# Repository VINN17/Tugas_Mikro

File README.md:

# 🚧 Building Automation System (BAS) untuk Pompa Air Jalan Tol
### Solusi Banjir dan Kemacetan saat Hujan Berkepanjangan

<div align="center">
  
</div>

                                                    https://github.com/user-attachments/assets/4135e06a-734f-496c-8481-714472587500

## 📚 Daftar Isi

1. [📌 Deskripsi Proyek](#-deskripsi-proyek)
2. [🎯 Tujuan Proyek](#-tujuan-proyek)
3. [🛠️ Teknologi dan Komponen](#️-teknologi-dan-komponen)
4. [⚙️ Cara Kerja Sistem](#️-cara-kerja-sistem)
5. [🧩 Diagram Alur Sistem](#-diagram-alur-sistem)
6. [🌟 Keunggulan Proyek](#-keunggulan-proyek)
7. [📈 Potensi Pengembangan](#-potensi-pengembangan)
8. [🤝 Kolaborasi & Dukungan](#-kolaborasi--dukungan)
9. [👥 Struktur Tim](#-struktur-tim)
10. [📩 Hubungi Kami](#-hubungi-kami)

---

## 📌 Deskripsi Proyek

**Building Automation Systems** ini dirancang untuk mengotomatisasi pengoperasian **pompa air pada jalan tol** guna mengatasi genangan atau banjir secara cepat dan efisien.

Dengan memanfaatkan sensor debit dan volume air, sistem ini mampu menghidupkan atau mematikan pompa secara otomatis berdasarkan data real-time, sehingga meningkatkan **keamanan** dan **kenyamanan** pengguna jalan.

> Dikembangkan berbasis **Arduino Uno** dan sistem monitoring berbasis GUI, proyek ini menawarkan solusi otomasi yang **andal**, **efisien**, dan **mudah diimplementasikan**.

---

## 🎯 Tujuan Proyek

* **Efisiensi Operasional Maksimal**
  Sistem mengeliminasi keterlambatan manual dan mengoptimalkan respons terhadap kondisi air.

* **Minimalkan Risiko Human Error**
  Pengambilan keputusan berbasis data sensor menghindari kesalahan dalam penanganan banjir.

* **Solusi Otomasi Biaya Terjangkau**
  Menggunakan komponen yang tersedia di pasaran dengan biaya rendah, ideal untuk skalabilitas.

---

## 🛠️ Teknologi dan Komponen

| Komponen           | Spesifikasi                                  |
| ------------------ | -------------------------------------------- |
| Mikrokontroler     | Arduino Uno                                  |
| Sensor Debit Air   | Pressure Sensor                              |
| Sensor Volume Air  | Ultrasonic / Water Level Sensor              |
| Aktuator           | Pompa Air + Relay Module                     |
| Antarmuka Pengguna | GUI berbasis Figma (Start/Stop, Monitoring)  |
| Komunikasi Data    | Serial / Wireless (pengembangan selanjutnya) |

---

## ⚙️ Cara Kerja Sistem

1. Sensor membaca **debit** dan **volume air** secara berkala.
2. Data dikirim ke mikrokontroler dan dibandingkan dengan nilai **set point**.
3. **Logika Kendali Otomatis**:

   * Jika data melebihi ambang → **Pompa ON**
   * Jika data aman → **Pompa OFF**
4. Status sistem ditampilkan pada GUI untuk **monitoring real-time**.
5. Operator dapat melakukan **manual override** dari GUI bila dibutuhkan.

---

## 🧩 Diagram Alur Sistem

**Penjelasan Alur:**

* Sistem dimulai melalui tampilan GUI.

* Pengguna memilih mode: **Auto** atau **Manual**.

  * **Auto**: sensor membaca data → kirim ke GUI → kontrol pompa otomatis.
  * **Manual**: pengguna dapat menyalakan/mematikan pompa secara langsung.

* Sistem akan terus berjalan sampai dihentikan manual oleh operator.

---

## 💻 PCB

Diatas  merupakan desain PCB jadi 

---

## 🌟 Keunggulan Proyek

* ✅ **Respon Real-Time** terhadap potensi banjir.
* ✅ **Kontrol Terpusat & Mudah** dari satu GUI.
* ✅ **Terintegrasi dengan IoT/SCADA** untuk masa depan.
* ✅ **Desain Scalable** & mudah diadaptasi ke area baru.
* ✅ **Ramah Anggaran** untuk implementasi massal.

---

## 📈 Potensi Pengembangan

* 🌐 **Integrasi ke IoT Cloud**: akses global & notifikasi otomatis.
* 🔔 **Peringatan SMS/WhatsApp** saat kondisi kritis.
* 🧠 **Prediksi Banjir Berbasis AI**: analisis historis dengan Machine Learning.
* 🏙️ **Kompatibel dengan Smart City Infrastructure**.

---

## 🤝 Kolaborasi & Dukungan

Kami membuka peluang kerja sama dengan:

* 🔧 **Investor teknologi** yang tertarik pada otomasi infrastruktur.
* 🛣️ **Pemerintah / Operator Jalan Tol** untuk penerapan langsung.
* 🧪 **Startup atau perusahaan R\&D** yang ingin mengembangkan solusi pintar dan berdampak.

> 🎯 Kami siap melakukan presentasi, demo proyek, dan diskusi lanjutan bersama mitra strategis.

---

## 👥 Struktur Tim

| NRP        | Nama    | Peran Utama              |
| ---------- | ------- | ------------------------ |
| 2123600010 | Imam    | Project Manager          |
| 2123600014 | Ferri   | Desain PCB               |
| 2123600004 | Robith  | Spesialis Hardware       |
| 2123600030 | Zach    | Pengembang Software      |
| 2123600023 | Choirul | Desainer 3D              |
| 2123600019 | Andira  | Non-Teknis & Dokumentasi |

---

## 📩 Hubungi Kami

📧 Untuk kerja sama, pertanyaan, atau demo proyek:

**Email Project Manager**: [immarfn17@gmail.com](mailto:immarfn17@gmail.com)

https://github.com/user-attachments/assets/88c9bd39-f75d-4216-a4de-ee6d6c01959d
> 🚀 Mari bersama kita ciptakan masa depan infrastruktur jalan tol yang lebih **cerdas**, **aman**, dan **berkelanjutan**.

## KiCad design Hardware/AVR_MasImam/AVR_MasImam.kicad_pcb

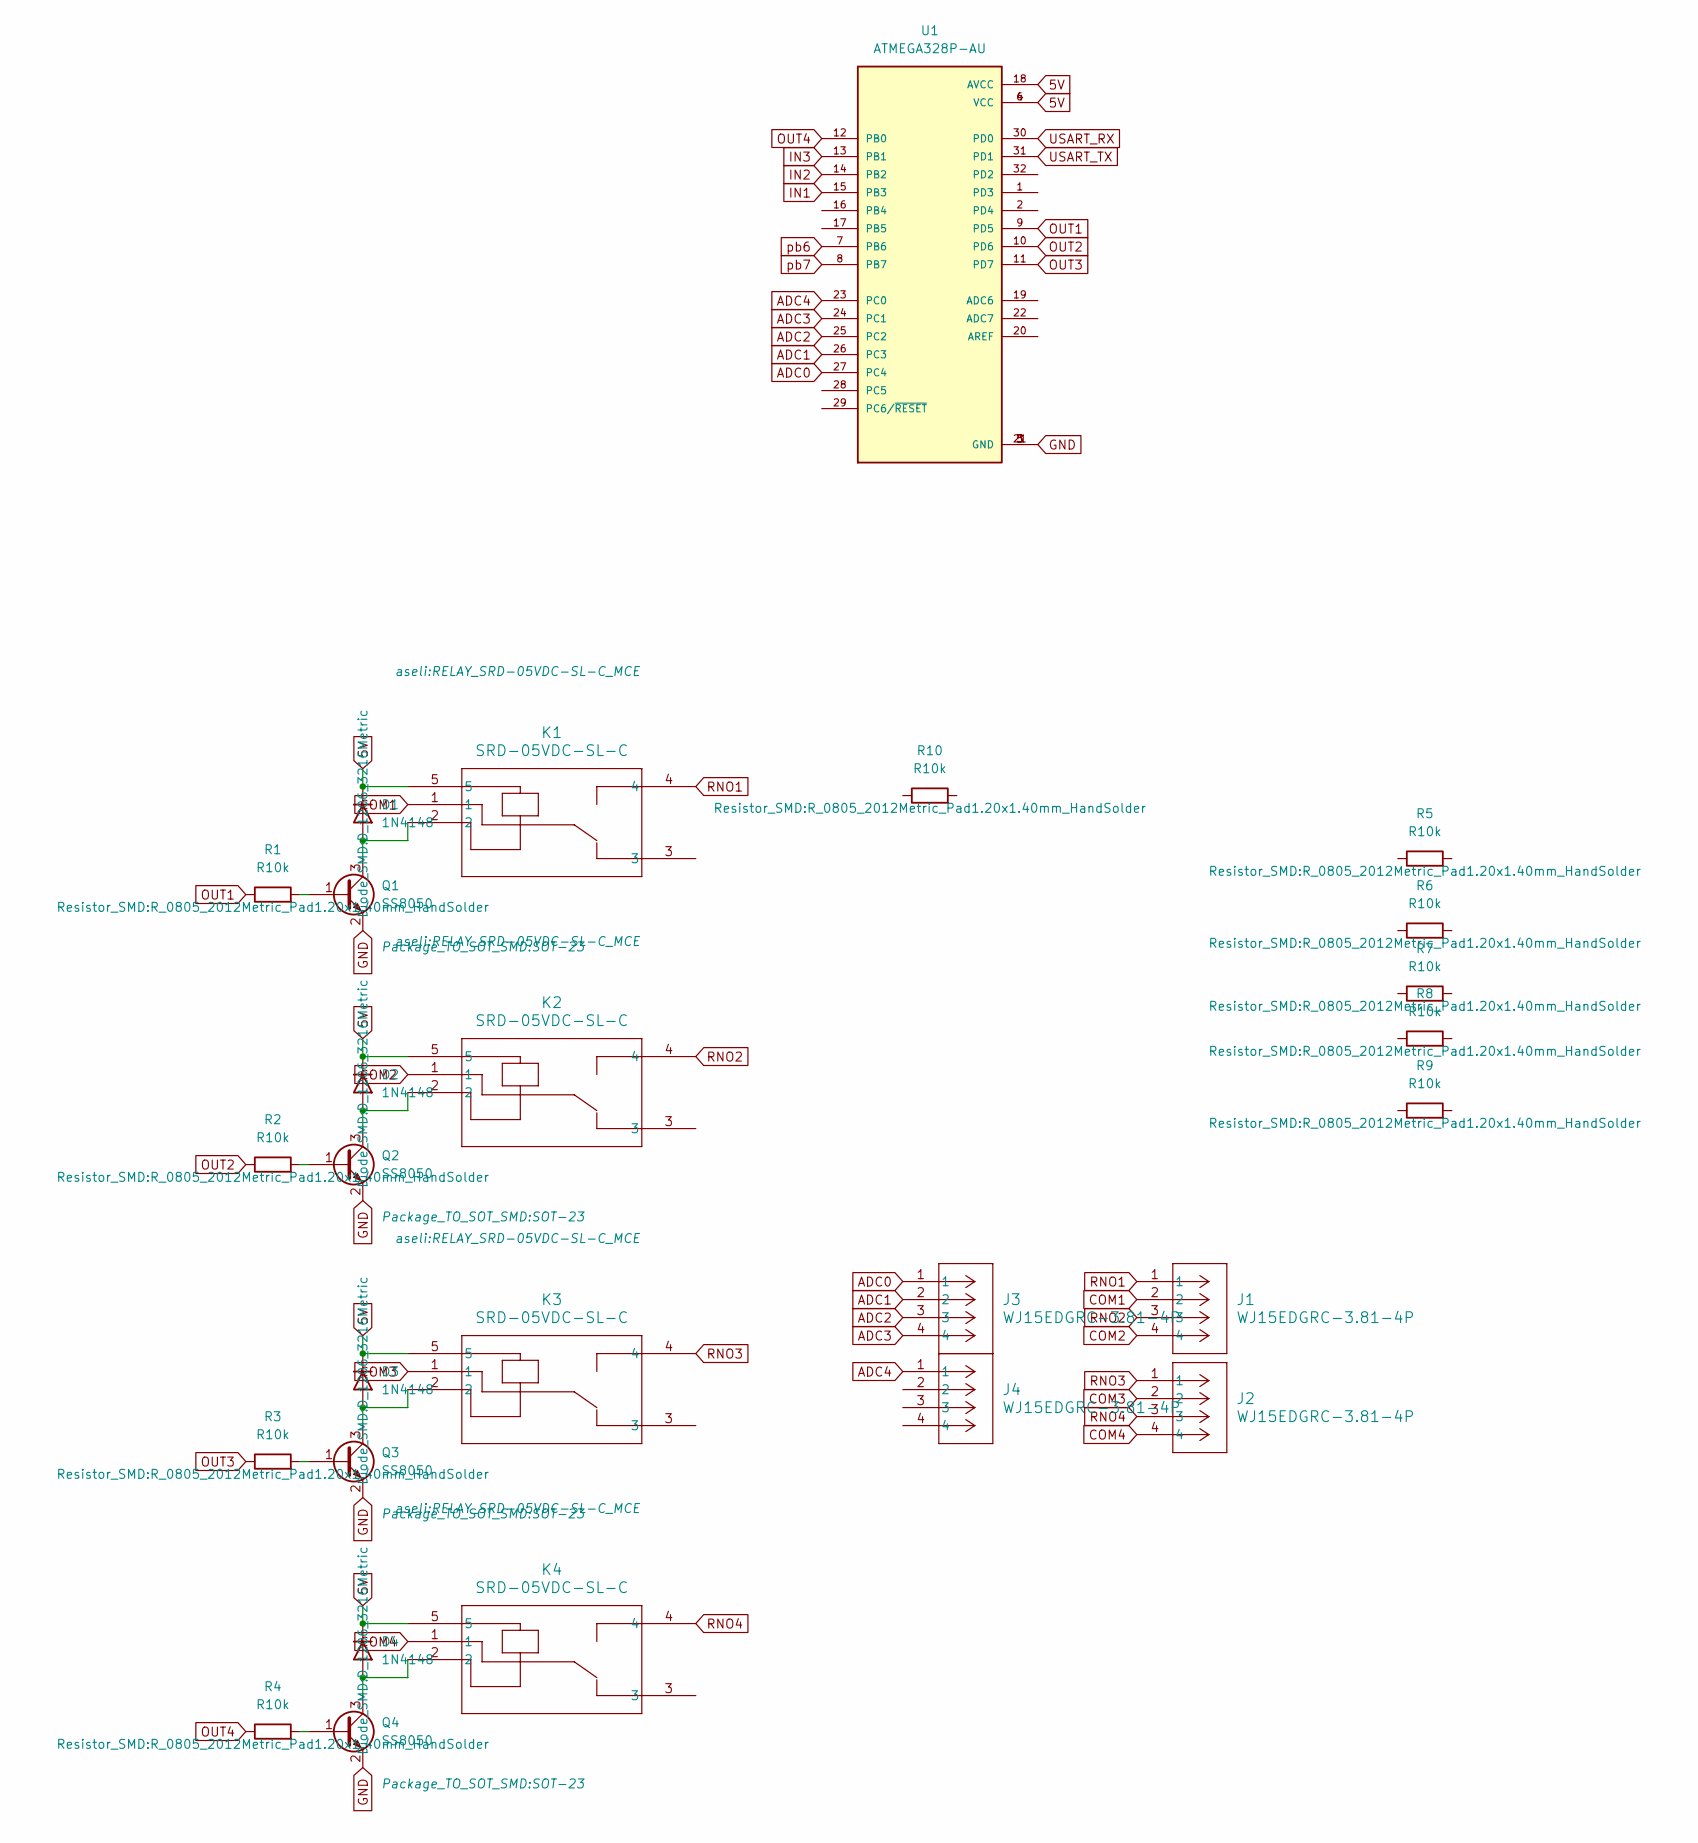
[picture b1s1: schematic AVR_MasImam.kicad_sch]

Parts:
D1, D2, D3, D4: 1N4148; D_1206_3216Metric
J1, J2, J3, J4: WJ15EDGRC-3.81-4P; CONN_WJ15EDGRC-3.81-4P_KAN
K1, K2, K3, K4: SRD-05VDC-SL-C; RELAY_SRD-05VDC-SL-C_MCE
Q1, Q2, Q3, Q4: SS8050; SOT-23
R1, R2, R3, R4, R5, R6, R7, R8, R9, R10: R10k; R_0805_2012Metric_Pad1.20x1.40mm_HandSolder
U1: ATMEGA328P-AU; QFP80P900X900X120-32N; PARTREV 8271A

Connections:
5V: D1.1 (K), D2.1 (K), D3.1 (K), D4.1 (K), K1.5, K2.5, K3.5, K4.5, U1.4 (VCC), U1.6 (VCC), U1.18 (AVCC); also elsewhere on the board
ADC0: J3.1, R5.2, U1.27 (PC4); also elsewhere on the board
ADC1: J3.2, R6.2, U1.26 (PC3); also elsewhere on the board
ADC2: J3.3, R7.2, U1.25 (PC2); also elsewhere on the board
ADC3: J3.4, R8.2, U1.24 (PC1); also elsewhere on the board
ADC4: J4.1, R9.2, U1.23 (PC0); also elsewhere on the board
COM1: J1.2, K1.1
COM2: J1.4, K2.1
COM3: J2.2, K3.1
COM4: J2.4, K4.1
GND: Q1.2 (E), Q2.2 (E), Q3.2 (E), Q4.2 (E), R5.1, R6.1, R7.1, R8.1, R9.1, U1.3 (GND), U1.5 (GND), U1.21 (GND); also elsewhere on the board
unnamed: D1.2 (A), K1.2, Q1.3 (C)
unnamed: D2.2 (A), K2.2, Q2.3 (C)
unnamed: D3.2 (A), K3.2, Q3.3 (C)
unnamed: D4.2 (A), K4.2, Q4.3 (C)
unnamed: Q1.1 (B), R1.2
unnamed: Q2.1 (B), R2.2
unnamed: Q3.1 (B), R3.2
unnamed: Q4.1 (B), R4.2
OUT1: R1.1, U1.9 (PD5); also elsewhere on the board
OUT2: R2.1, U1.10 (PD6); also elsewhere on the board
OUT3: R3.1, U1.11 (PD7); also elsewhere on the board
OUT4: R4.1, U1.12 (PB0); also elsewhere on the board
RNO1: J1.1, K1.4
RNO2: J1.3, K2.4
RNO3: J2.1, K3.4
RNO4: J2.3, K4.4

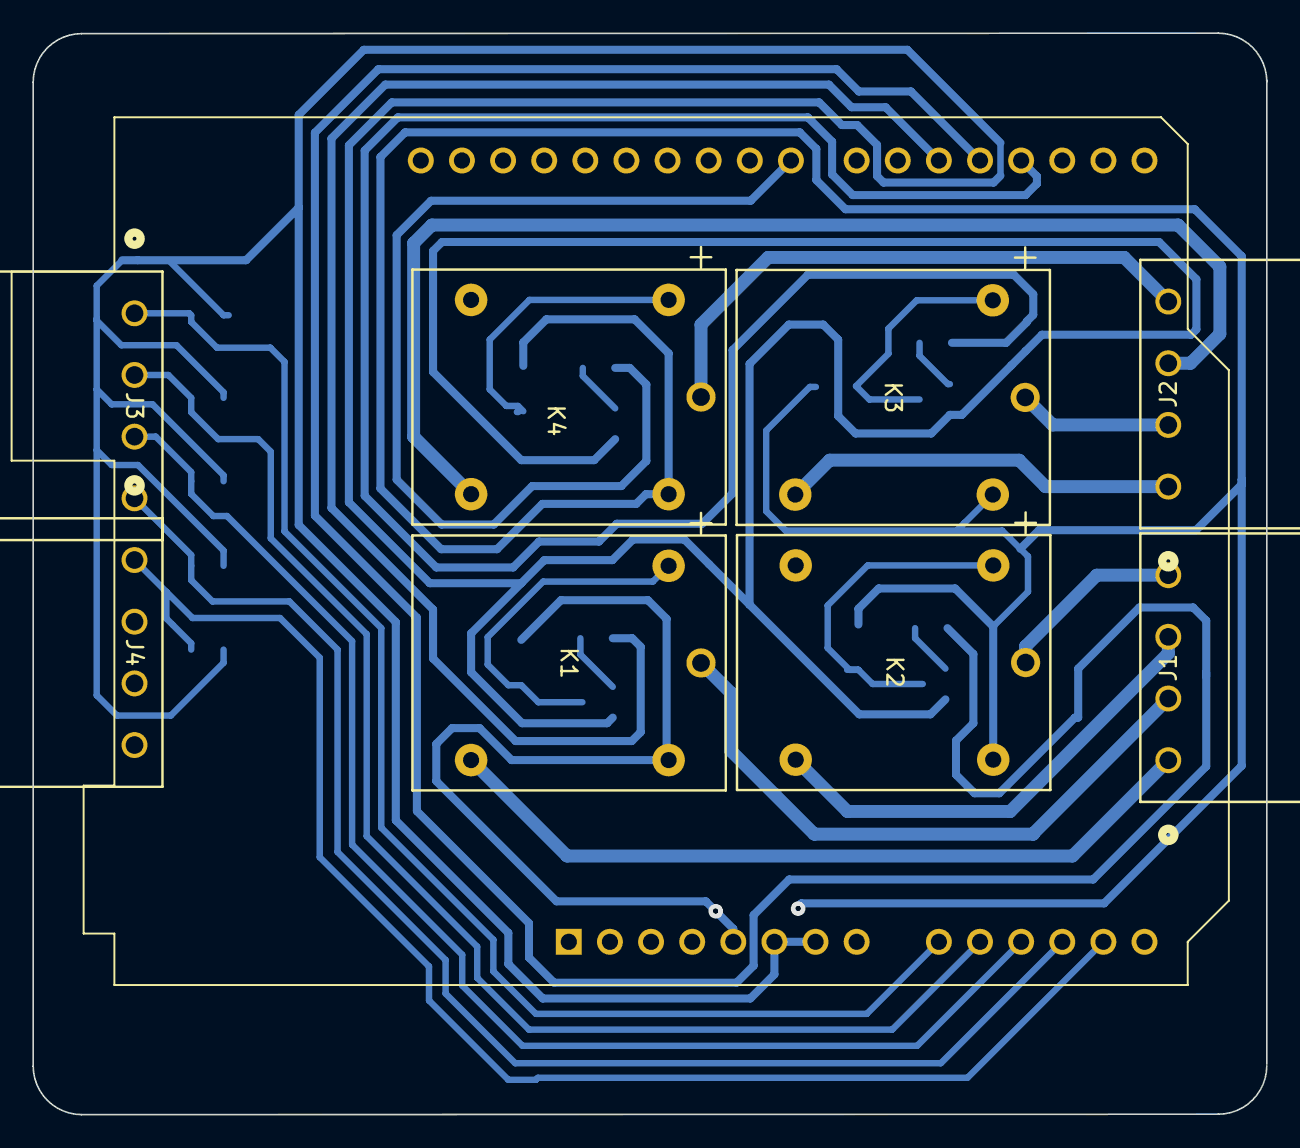
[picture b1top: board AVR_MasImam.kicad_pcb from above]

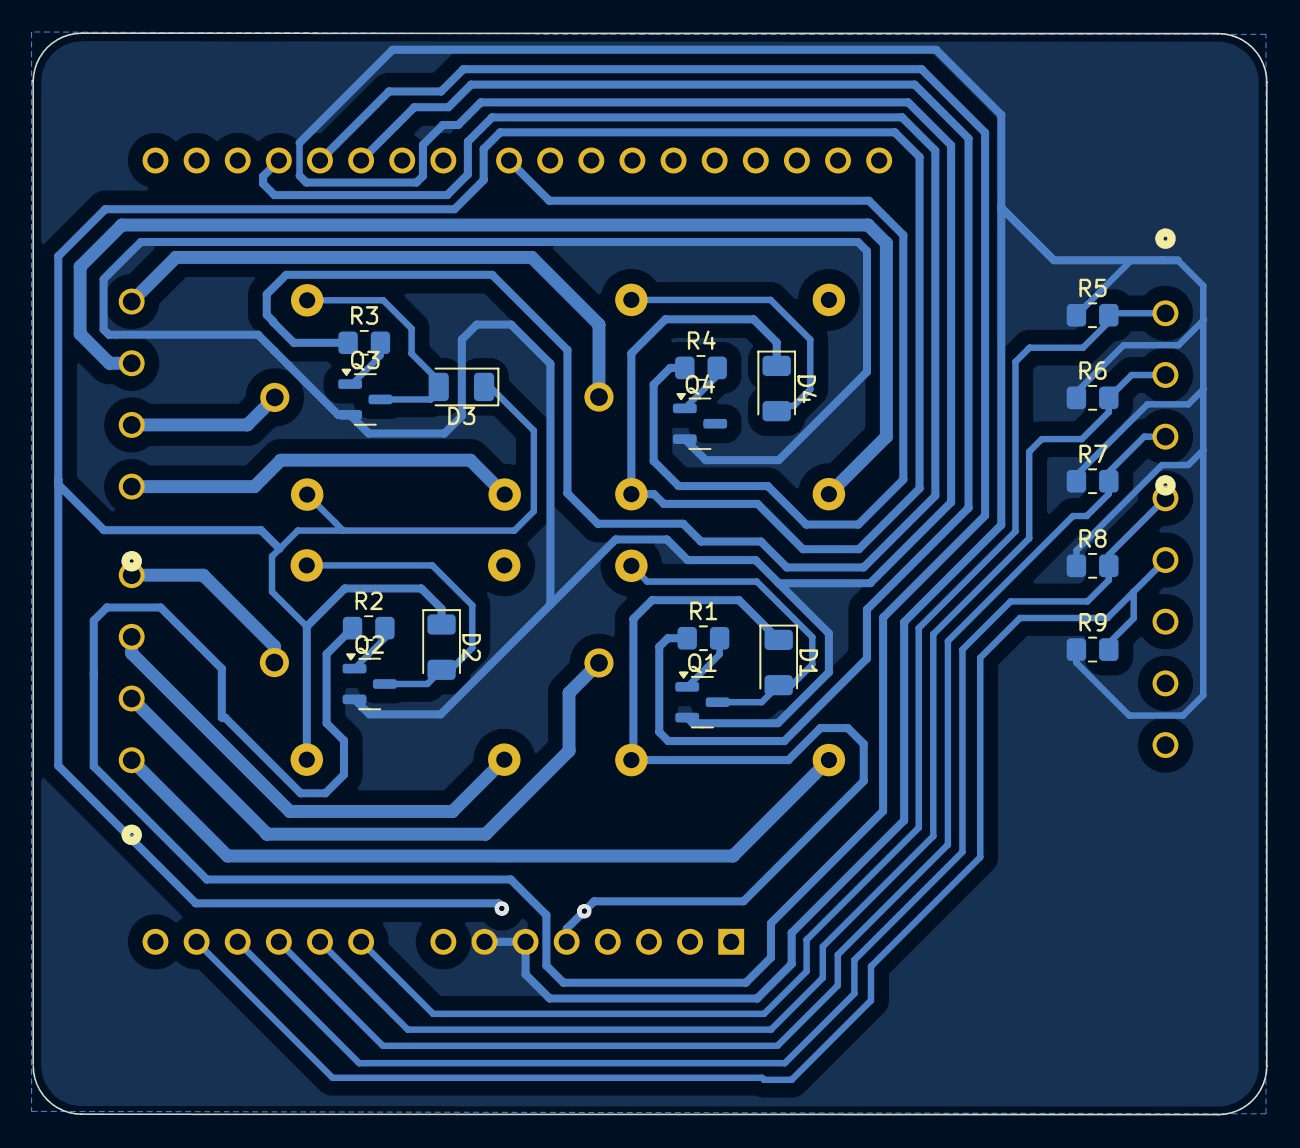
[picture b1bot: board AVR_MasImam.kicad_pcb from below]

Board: 2 copper layers, 76.2 x 66.8 mm, 26 parts (17 on the bottom side), 27 nets.

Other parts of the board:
A1: Arduino_UNO_R3

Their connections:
5V: A1.5 (+5V); also elsewhere on the board
ADC0: A1.9 (A0); also elsewhere on the board
ADC1: A1.10 (A1); also elsewhere on the board
ADC2: A1.11 (A2); also elsewhere on the board
ADC3: A1.12 (A3); also elsewhere on the board
ADC4: A1.13 (SDA/A4); also elsewhere on the board
GND: A1.6 (GND), A1.7 (GND); also elsewhere on the board
OUT1: A1.20 (D5); also elsewhere on the board
OUT2: A1.19 (D4); also elsewhere on the board
OUT3: A1.18 (D3); also elsewhere on the board
OUT4: A1.23 (D8); also elsewhere on the board

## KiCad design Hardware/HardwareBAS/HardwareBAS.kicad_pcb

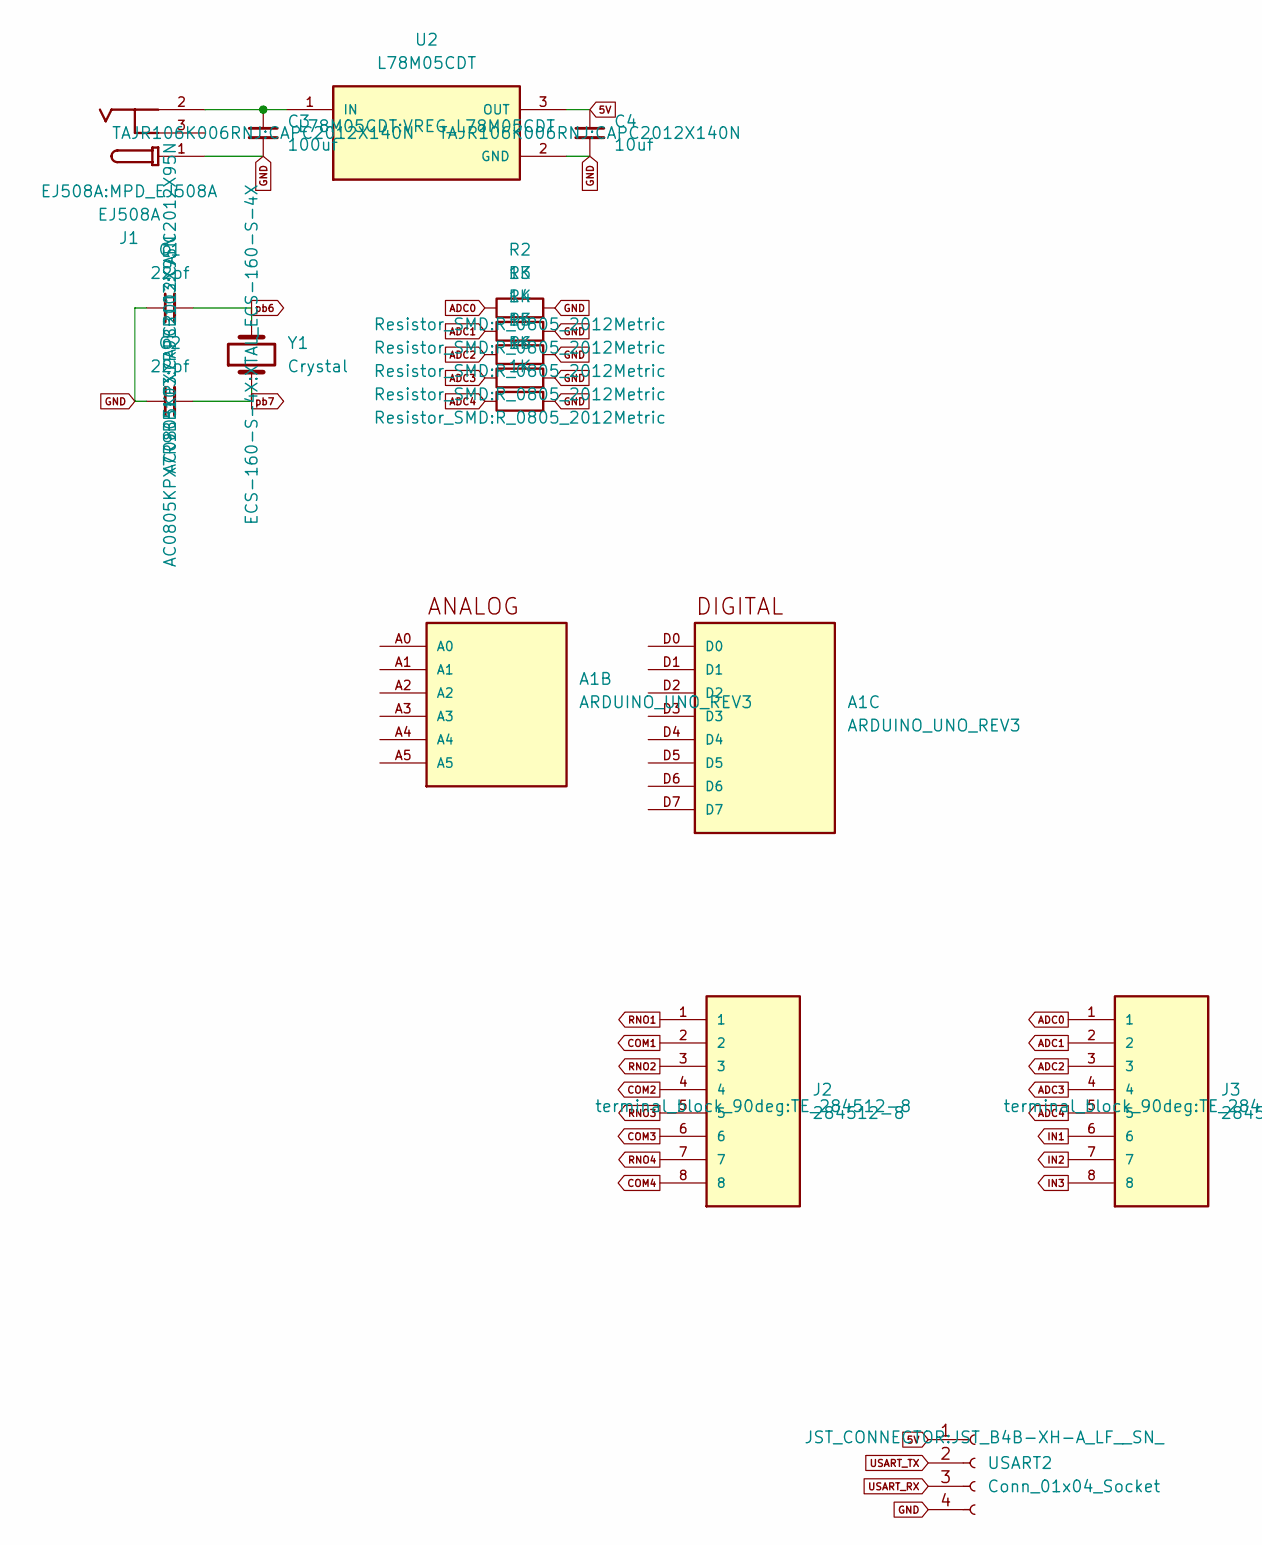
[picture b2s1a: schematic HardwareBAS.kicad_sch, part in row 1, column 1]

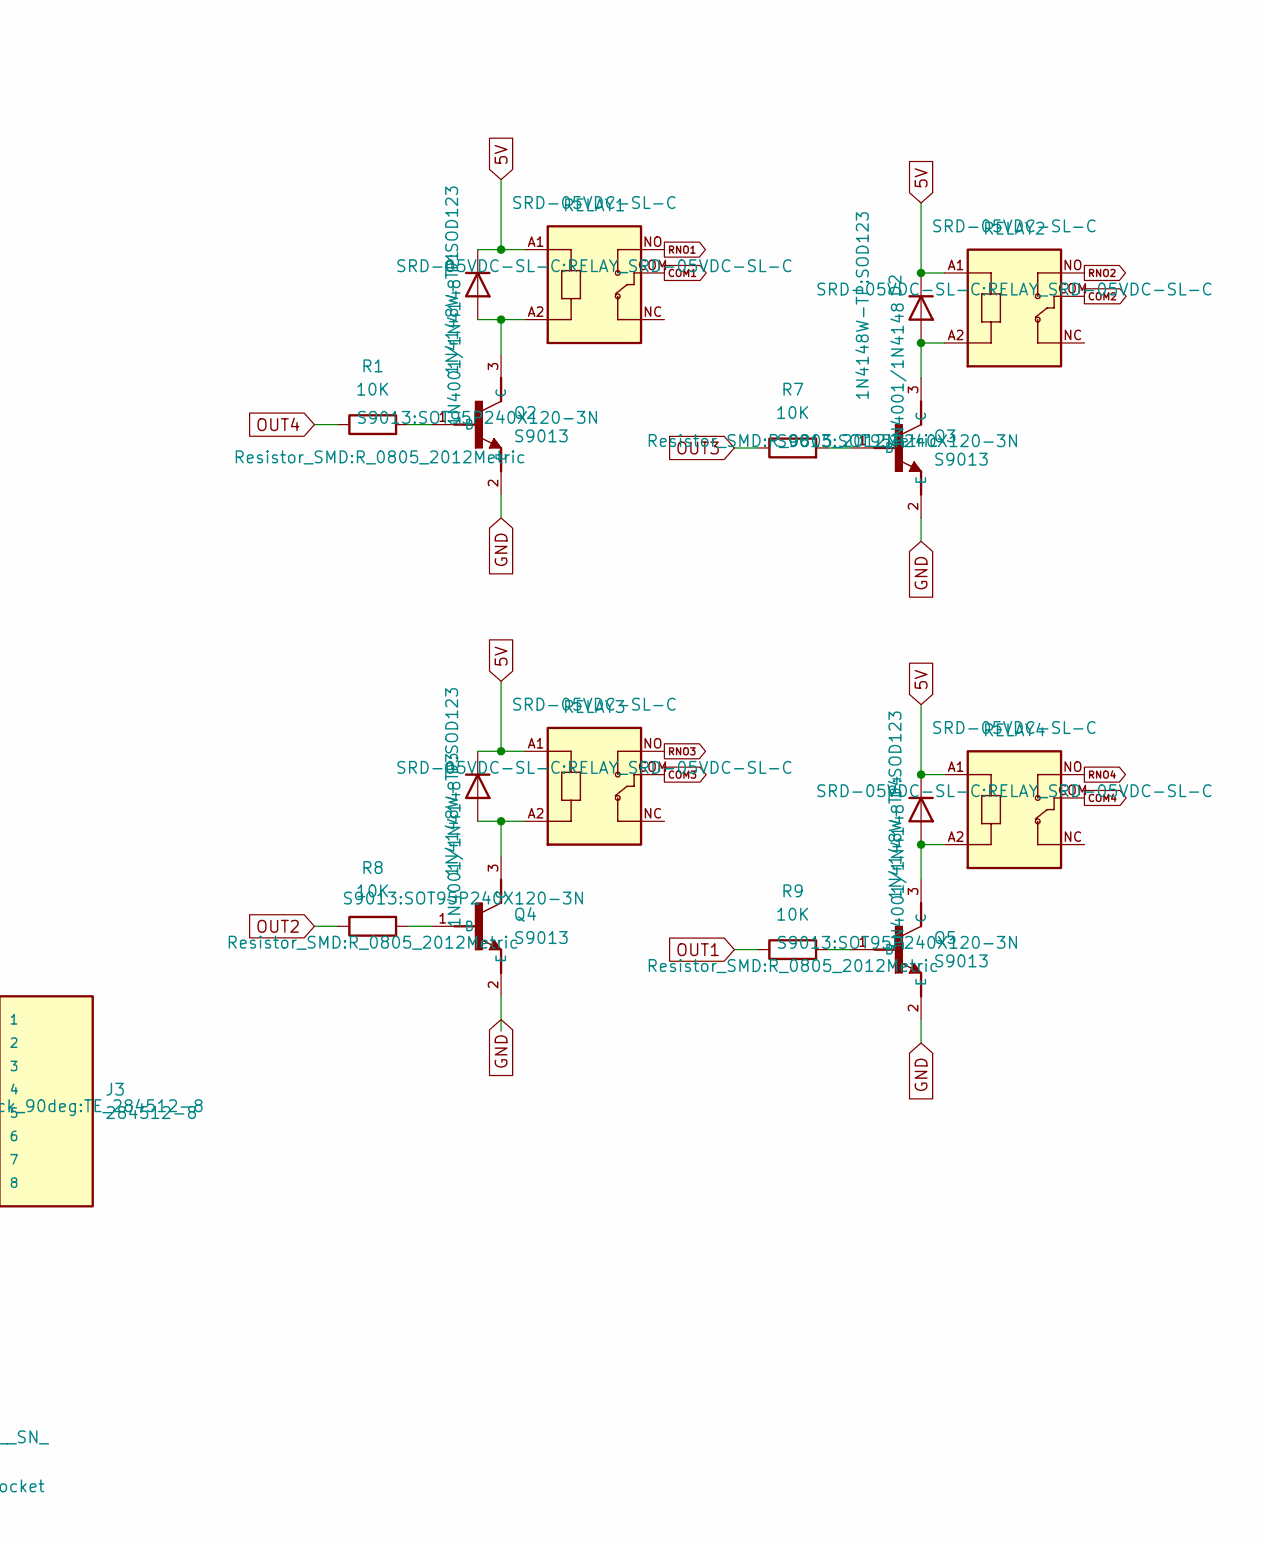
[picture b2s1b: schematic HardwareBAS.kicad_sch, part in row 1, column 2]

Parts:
A1: ARDUINO_UNO_REV3; ARDUINO_ARDUINO_UNO_REV3; PARTREV N/A
C1, C2: 22pf; CAPC2012X95N
C3: 100uf; CAPC2012X140N
C4: 10uf; CAPC2012X140N
D1, D2, D3, D4: 1N4001/1N4148; SOD123
J1: EJ508A; MPD_EJ508A; PARTREV J
J2, J3: 284512-8; TE_284512-8; PARTREV R
Q2, Q3, Q4, Q5: S9013; SOT95P240X120-3N
R1, R7, R8, R9: 10K; R_0805_2012Metric
R2, R3, R4, R5, R6: 1K; R_0805_2012Metric
RELAY1, RELAY2, RELAY3, RELAY4: SRD-05VDC-SL-C; RELAY_SRD-05VDC-SL-C
U2: L78M05CDT; VREG_L78M05CDT; PARTREV 24
USART2: Conn_01x04_Socket; JST_B4B-XH-A_LF__SN_
Y1: Crystal; XTAL_ECS-160-S-4X

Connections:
5V: C4.1, D1.1 (K), D2.1 (K), D3.1 (K), D4.1 (K), RELAY1.A1, RELAY2.A1, RELAY3.A1, RELAY4.A1, U2.3 (OUT), USART2.1
ADC0: J3.1, R2.1
ADC1: J3.2, R3.1
ADC2: J3.3, R4.1
ADC3: J3.4, R5.1
ADC4: J3.5, R6.1
COM1: J2.2, RELAY1.COM
COM2: J2.4, RELAY2.COM
COM3: J2.6, RELAY3.COM
COM4: J2.8, RELAY4.COM
GND: C1.1, C2.1, C3.2, C4.2, J1.1, Q2.2 (E), Q3.2 (E), Q4.2 (E), Q5.2 (E), R2.2, R3.2, R4.2, R5.2, R6.2, U2.2 (GND), USART2.4
IN1: J3.6
IN2: J3.7
IN3: J3.8
unnamed: D1.2 (A), Q2.3 (C), RELAY1.A2
unnamed: D2.2 (A), Q3.3 (C), RELAY2.A2
unnamed: D3.2 (A), Q4.3 (C), RELAY3.A2
unnamed: D4.2 (A), Q5.3 (C), RELAY4.A2
unnamed: Q2.1 (B), R1.2
unnamed: Q3.1 (B), R7.2
unnamed: Q4.1 (B), R8.2
unnamed: Q5.1 (B), R9.2
unnamed: C3.1, J1.2, U2.1 (IN)
OUT1: R9.1
OUT2: R8.1
OUT3: R7.1
OUT4: R1.1
RNO1: J2.1, RELAY1.NO
RNO2: J2.3, RELAY2.NO
RNO3: J2.5, RELAY3.NO
RNO4: J2.7, RELAY4.NO
USART_RX: USART2.3
USART_TX: USART2.2
pb6: C1.2, Y1.2
pb7: C2.2, Y1.1

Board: 2 copper layers, 32 parts (0 on the bottom side), 26 nets, no tracks yet.

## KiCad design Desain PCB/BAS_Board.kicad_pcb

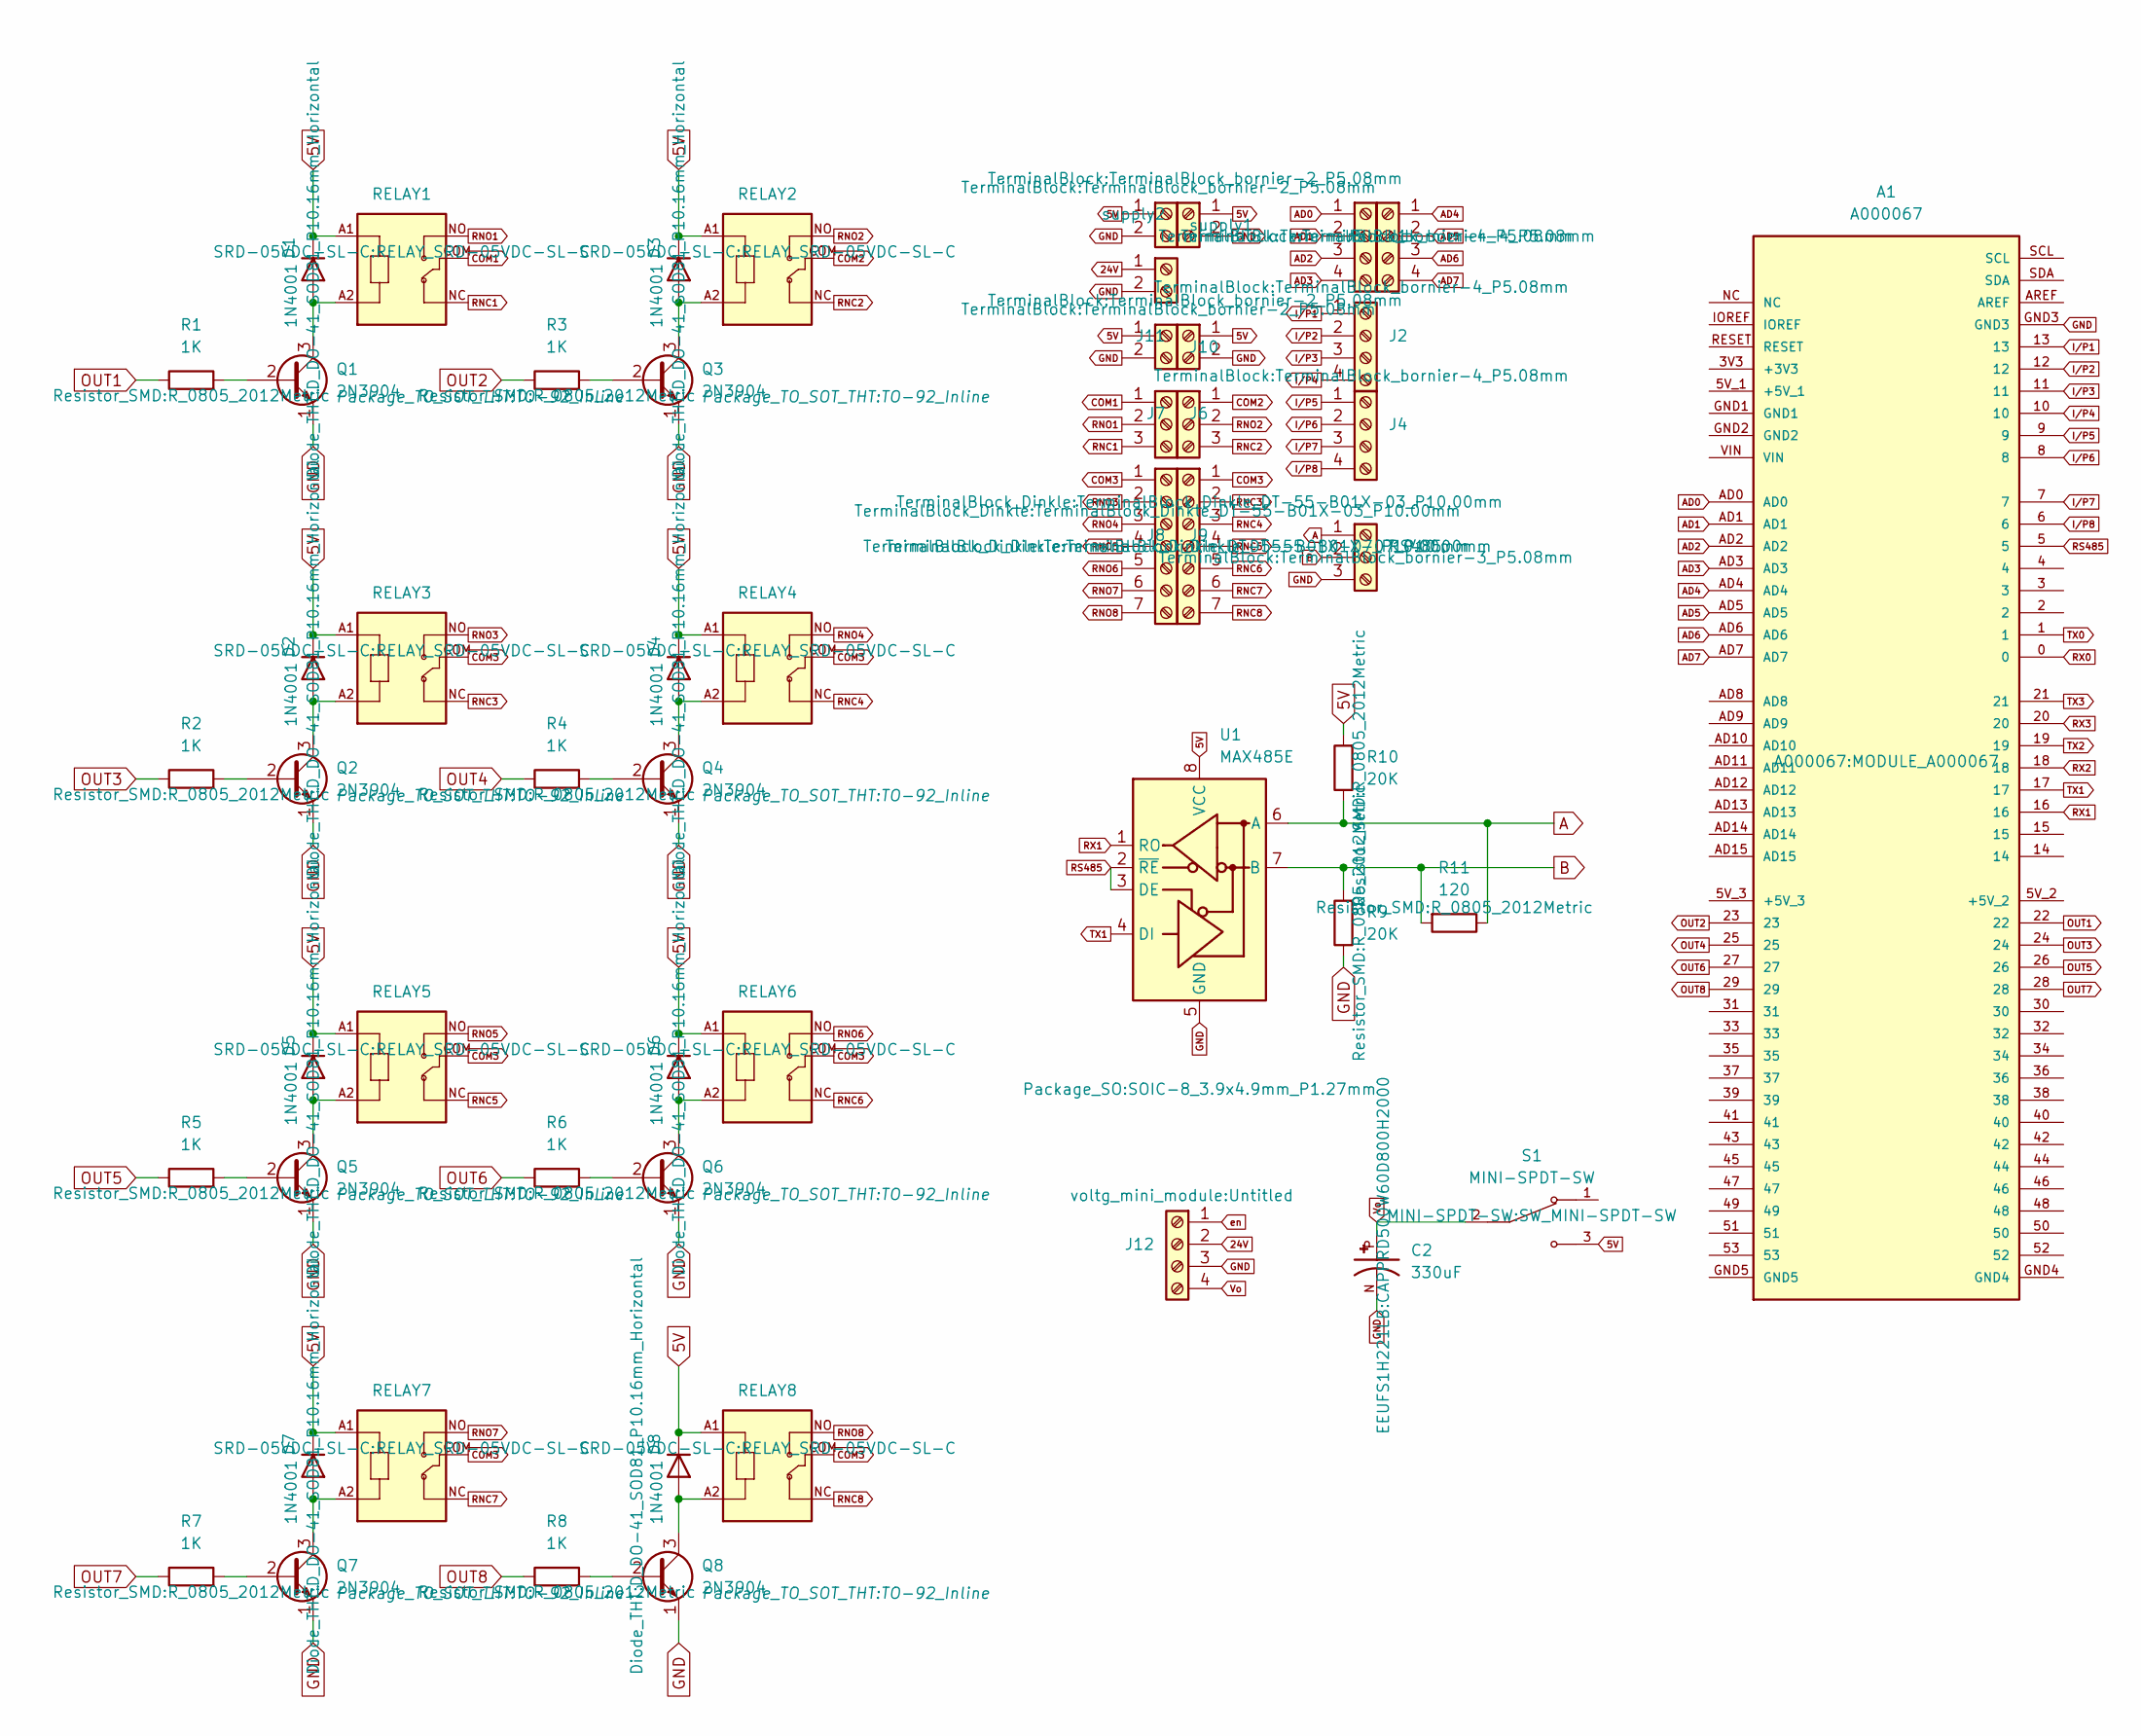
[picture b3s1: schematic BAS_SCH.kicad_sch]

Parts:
A1: A000067; MODULE_A000067; PARTREV 3; DigiKey_Part_Number 1050-1018-ND
C2: 330uF; CAPPRD500W60D800H2000; PARTREV 28-FEB-20; DigiKey_Part_Number P122329CT-ND
D1, D2, D3, D4, D5, D6, D7, D8: 1N4001; D_DO-41_SOD81_P10.16mm_Horizontal
J1, J2, J4, J5: Screw_Terminal_01x04; TerminalBlock_bornier-4_P5.08mm
J6, J7: Screw_Terminal_01x03; TerminalBlock_Dinkle_DT-55-B01X-03_P10.00mm
J8, J9: Screw_Terminal_01x07; TerminalBlock_Dinkle_DT-55-B01X-07_P10.00mm
J10, J11: Screw_Terminal_01x02; TerminalBlock_bornier-2_P5.08mm
J12: Screw_Terminal_01x04; Untitled
Power1: Screw_Terminal_01x02; TerminalBlock_Dinkle_DT-55-B01X-02_P10.00mm
Q1, Q2, Q3, Q4, Q5, Q6, Q7, Q8: 2N3904; TO-92_Inline
R1, R2, R3, R4, R5, R6, R7, R8: 1K; R_0805_2012Metric
R9, R10: 20K; R_0805_2012Metric
R11: 120; R_0805_2012Metric
RELAY1, RELAY2, RELAY3, RELAY4, RELAY5, RELAY6, RELAY7, RELAY8: SRD-05VDC-SL-C; RELAY_SRD-05VDC-SL-C
RS485: Screw_Terminal_01x03; TerminalBlock_bornier-3_P5.08mm
S1: MINI-SPDT-SW; SW_MINI-SPDT-SW; PARTREV C
U1: MAX485E; SOIC-8_3.9x4.9mm_P1.27mm
supply1, supply2: Screw_Terminal_01x02; TerminalBlock_bornier-2_P5.08mm

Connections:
5V: D1.1 (K), D2.1 (K), D3.1 (K), D4.1 (K), D5.1 (K), D6.1 (K), D7.1 (K), D8.1 (K), J10.1, J11.1, R10.2, RELAY1.A1, RELAY2.A1, RELAY3.A1, RELAY4.A1, RELAY5.A1, RELAY6.A1, RELAY7.A1, RELAY8.A1, S1.3, U1.8 (VCC), supply1.1, supply2.1
24V: J12.2, Power1.1
A: R10.1, R11.1, RS485.1, U1.6 (A)
AD0: A1.AD0, J1.1
AD1: A1.AD1, J1.2
AD2: A1.AD2, J1.3
AD3: A1.AD3, J1.4
AD4: A1.AD4, J5.1
AD5: A1.AD5, J5.2
AD6: A1.AD6, J5.3
AD7: A1.AD7, J5.4
B: R9.2, R11.2, RS485.2, U1.7 (B)
COM1: J6.1, RELAY1.COM
COM2: J7.1, RELAY2.COM
COM3: J8.1, J9.1, RELAY3.COM, RELAY4.COM, RELAY5.COM, RELAY6.COM, RELAY7.COM, RELAY8.COM
GND: A1.GND3, C2.N, J10.2, J11.2, J12.3, Power1.2, Q1.1 (E), Q2.1 (E), Q3.1 (E), Q4.1 (E), Q5.1 (E), Q6.1 (E), Q7.1 (E), Q8.1 (E), R9.1, RS485.3, U1.5 (GND), supply1.2, supply2.2
I/P1: A1.13, J2.1
I/P2: A1.12, J2.2
I/P3: A1.11, J2.3
I/P4: A1.10, J2.4
I/P5: A1.9, J4.1
I/P6: A1.8, J4.2
I/P7: A1.7, J4.3
I/P8: A1.6, J4.4
unnamed: D1.2 (A), Q1.3 (C), RELAY1.A2
unnamed: D2.2 (A), Q2.3 (C), RELAY3.A2
unnamed: D3.2 (A), Q3.3 (C), RELAY2.A2
unnamed: D4.2 (A), Q4.3 (C), RELAY4.A2
unnamed: D5.2 (A), Q5.3 (C), RELAY5.A2
unnamed: D6.2 (A), Q6.3 (C), RELAY6.A2
unnamed: D7.2 (A), Q7.3 (C), RELAY7.A2
unnamed: D8.2 (A), Q8.3 (C), RELAY8.A2
unnamed: Q1.2 (B), R1.2
unnamed: Q2.2 (B), R2.2
unnamed: Q3.2 (B), R3.2
unnamed: Q4.2 (B), R4.2
unnamed: Q5.2 (B), R5.2
unnamed: Q6.2 (B), R6.2
unnamed: Q7.2 (B), R7.2
unnamed: Q8.2 (B), R8.2
OUT1: A1.22, R1.1
OUT2: A1.23, R3.1
OUT3: A1.24, R2.1
OUT4: A1.25, R4.1
OUT5: A1.26, R5.1
OUT6: A1.27, R6.1
OUT7: A1.28, R7.1
OUT8: A1.29, R8.1
RNC1: J6.3, RELAY1.NC
RNC2: J7.3, RELAY2.NC
RNC3: J8.2, RELAY3.NC
RNC4: J8.3, RELAY4.NC
RNC5: J8.4, RELAY5.NC
RNC6: J8.5, RELAY6.NC
RNC7: J8.6, RELAY7.NC
RNC8: J8.7, RELAY8.NC
RNO1: J6.2, RELAY1.NO
RNO2: J7.2, RELAY2.NO
RNO3: J9.2, RELAY3.NO
RNO4: J9.3, RELAY4.NO
RNO5: J9.4, RELAY5.NO
RNO6: J9.5, RELAY6.NO
RNO7: J9.6, RELAY7.NO
RNO8: J9.7, RELAY8.NO
RS485: A1.5, U1.2 (~RE), U1.3 (DE)
RX0: A1.0
RX1: A1.16, U1.1 (RO)
RX2: A1.18
RX3: A1.20
TX0: A1.1
TX1: A1.17, U1.4 (DI)
TX2: A1.19
TX3: A1.21
Vo: C2.P, J12.4, S1.2
en: J12.1
